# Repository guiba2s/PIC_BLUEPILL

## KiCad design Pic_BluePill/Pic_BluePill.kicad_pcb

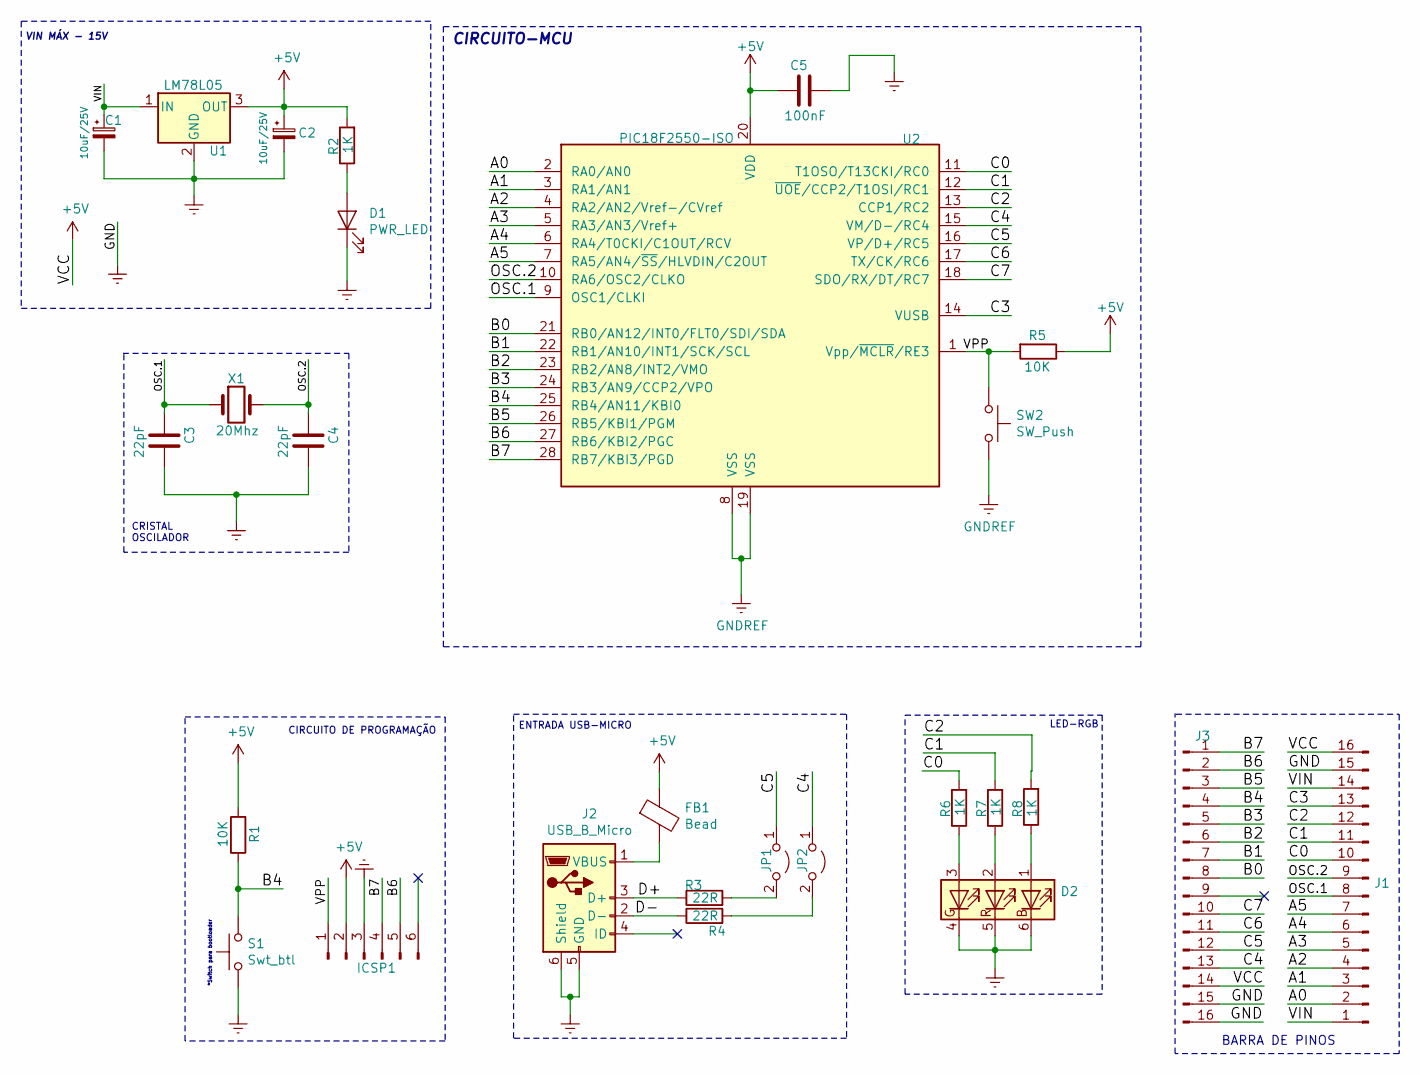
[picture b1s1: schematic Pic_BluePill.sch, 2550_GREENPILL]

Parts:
C1, C2: 10uF/25V; CP_Elec_4x4.5
C3, C4: 22pF; C_0603_1608Metric
C5: 100nF; C_0603_1608Metric
D1: PWR_LED; LED_0805_2012Metric
D2: SMLVN6RGB; LED_ROHM_SMLVN6
FB1: Bead; C_0805_2012Metric_Pad1.15x1.40mm_HandSolder
ICSP1: Conn_01x06_Male; PinHeader_1x06_P2.54mm_Vertical
J1, J3: Conn_01x16_Male; PinHeader_1x16_P2.54mm_Vertical
J2: USB_B_Micro; USB_Micro-B_Molex_47346-0001
JP1, JP2: Jumper_2_Open; SolderJumper-3_P1.3mm_Open_Pad1.0x1.5mm_NumberLabels
R1, R5: 10K; R_0603_1608Metric_Pad1.05x0.95mm_HandSolder
R2, R6, R7, R8: 1K; R_0603_1608Metric_Pad1.05x0.95mm_HandSolder
R3, R4: 22R; R_0603_1608Metric_Pad1.05x0.95mm_HandSolder
S1: Swt_btl; SW_SPST_B3U-1000P
SW2: SW_Push; SW_SPST_B3U-1000P
U1: LM78L05; TO-252-2
U2: PIC18F2550-ISO; SOIC-28W_7.5x17.9mm_P1.27mm
X1: 20Mhz; Crystal_SMD_HC49-SD

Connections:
+5V: C2.1, C5.1, FB1.1, ICSP1.2, J1.16, J3.14, R1.2, R2.2, R5.1, U1.3 (OUT), U2.20 (VDD)
/A0: J1.2, U2.2 (RA0/AN0)
/A1: J1.3, U2.3 (RA1/AN1)
/A2: J1.4, U2.4 (RA2/AN2/Vref-/CVref)
/A3: J1.5, U2.5 (RA3/AN3/Vref+)
/A4: J1.6, U2.6 (RA4/T0CKI/C1OUT/RCV)
/A5: J1.7, U2.7 (RA5/AN4/~SS~/HLVDIN/C2OUT)
/B0: J3.8, U2.21 (RB0/AN12/INT0/FLT0/SDI/SDA)
/B1: J3.7, U2.22 (RB1/AN10/INT1/SCK/SCL)
/B2: J3.6, U2.23 (RB2/AN8/INT2/VMO)
/B3: J3.5, U2.24 (RB3/AN9/CCP2/VPO)
/B4: J3.4, R1.1, S1.2, U2.25 (RB4/AN11/KBI0)
/B5: J3.3, U2.26 (RB5/KBI1/PGM)
/B6: ICSP1.5, J3.2, U2.27 (RB6/KBI2/PGC)
/B7: ICSP1.4, J3.1, U2.28 (RB7/KBI3/PGD)
/C0: J1.10, R6.2, U2.11 (T1OSO/T13CKI/RC0)
/C1: J1.11, R7.2, U2.12 (~UOE~/CCP2/T1OSI/RC1)
/C2: J1.12, R8.2, U2.13 (CCP1/RC2)
/C3: J1.13, U2.14 (VUSB)
/C4: J3.13, JP2.1 (A), U2.15 (VM/D-/RC4)
/C5: J3.12, JP1.1 (A), U2.16 (VP/D+/RC5)
/C6: J3.11, U2.17 (TX/CK/RC6)
/C7: J3.10, U2.18 (SDO/RX/DT/RC7)
/D+: J2.3 (D+), R3.1
/D-: J2.2 (D-), R4.1
/OSC.1: C3.1, J1.8, U2.9 (OSC1/CLKI), X1.1
/OSC.2: C4.1, J1.9, U2.10 (RA6/OSC2/CLKO), X1.2
/VIN: C1.1, J1.1, J1.14, U1.1 (IN)
/VPP: ICSP1.1, R5.2, SW2.1, U2.1 (Vpp/~MCLR~/RE3)
GNDREF: C1.2, C2.2, C3.2, C4.2, C5.2, D1.1 (K), D2.4 (GK), D2.5 (RK), D2.6 (BK), ICSP1.3, J1.15, J2.5 (GND), J2.6 (Shield), J3.15, J3.16, S1.1, SW2.2, U1.2 (GND), U2.8 (VSS), U2.19 (VSS)
unnamed: D1.2 (A), R2.1
unnamed: D2.1 (BA), R8.1
unnamed: D2.2 (RA), R7.1
unnamed: D2.3 (GA), R6.1
unnamed: FB1.2, J2.1 (VBUS)
unnamed: JP1.2 (B), R3.2
unnamed: JP2.2 (B), R4.2

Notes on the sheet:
VIN MÁX - 15V
*Switch para bootloader
CIRCUITO DE PROGRAMAÇÃO
ENTRADA USB-MICRO
LED-RGB
CIRCUITO-MCU
CRISTAL OSCILADOR
BARRA DE PINOS

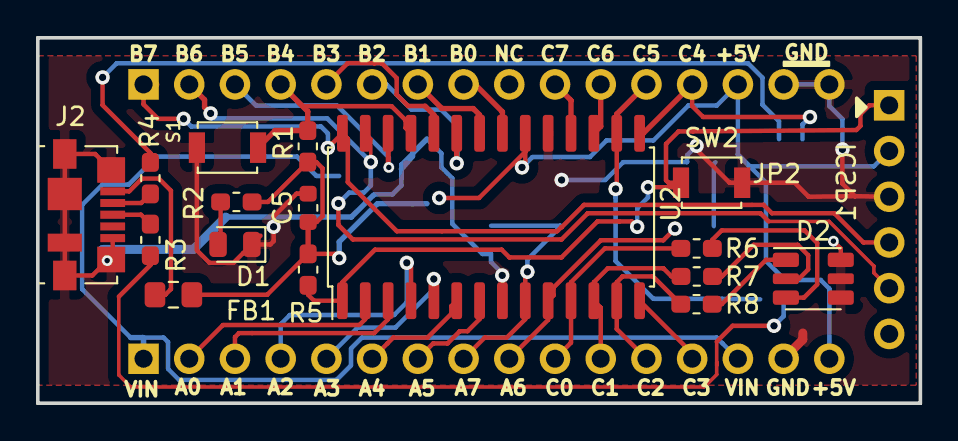
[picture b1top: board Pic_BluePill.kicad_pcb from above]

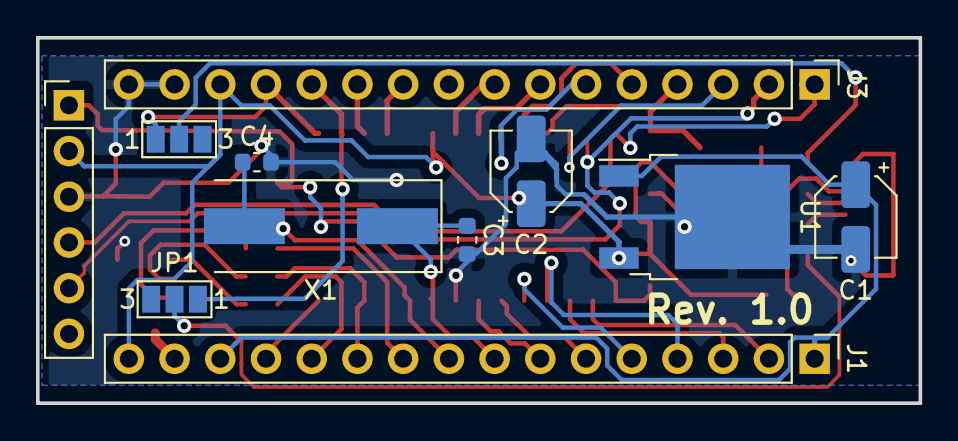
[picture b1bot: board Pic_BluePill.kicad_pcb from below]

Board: 2 copper layers, 49.0 x 20.3 mm, 27 parts (11 on the bottom side), 37 nets.

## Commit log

2020-06-26 Desenvolvimento Esquemático
2020-06-28 Desenvolvimento Hardware
2020-07-01 Finalização da Placa - sem arquivos de fabricação
2020-07-01 Criação da pasta Referências
2020-07-01 Inclusão de silk das ports do CI
